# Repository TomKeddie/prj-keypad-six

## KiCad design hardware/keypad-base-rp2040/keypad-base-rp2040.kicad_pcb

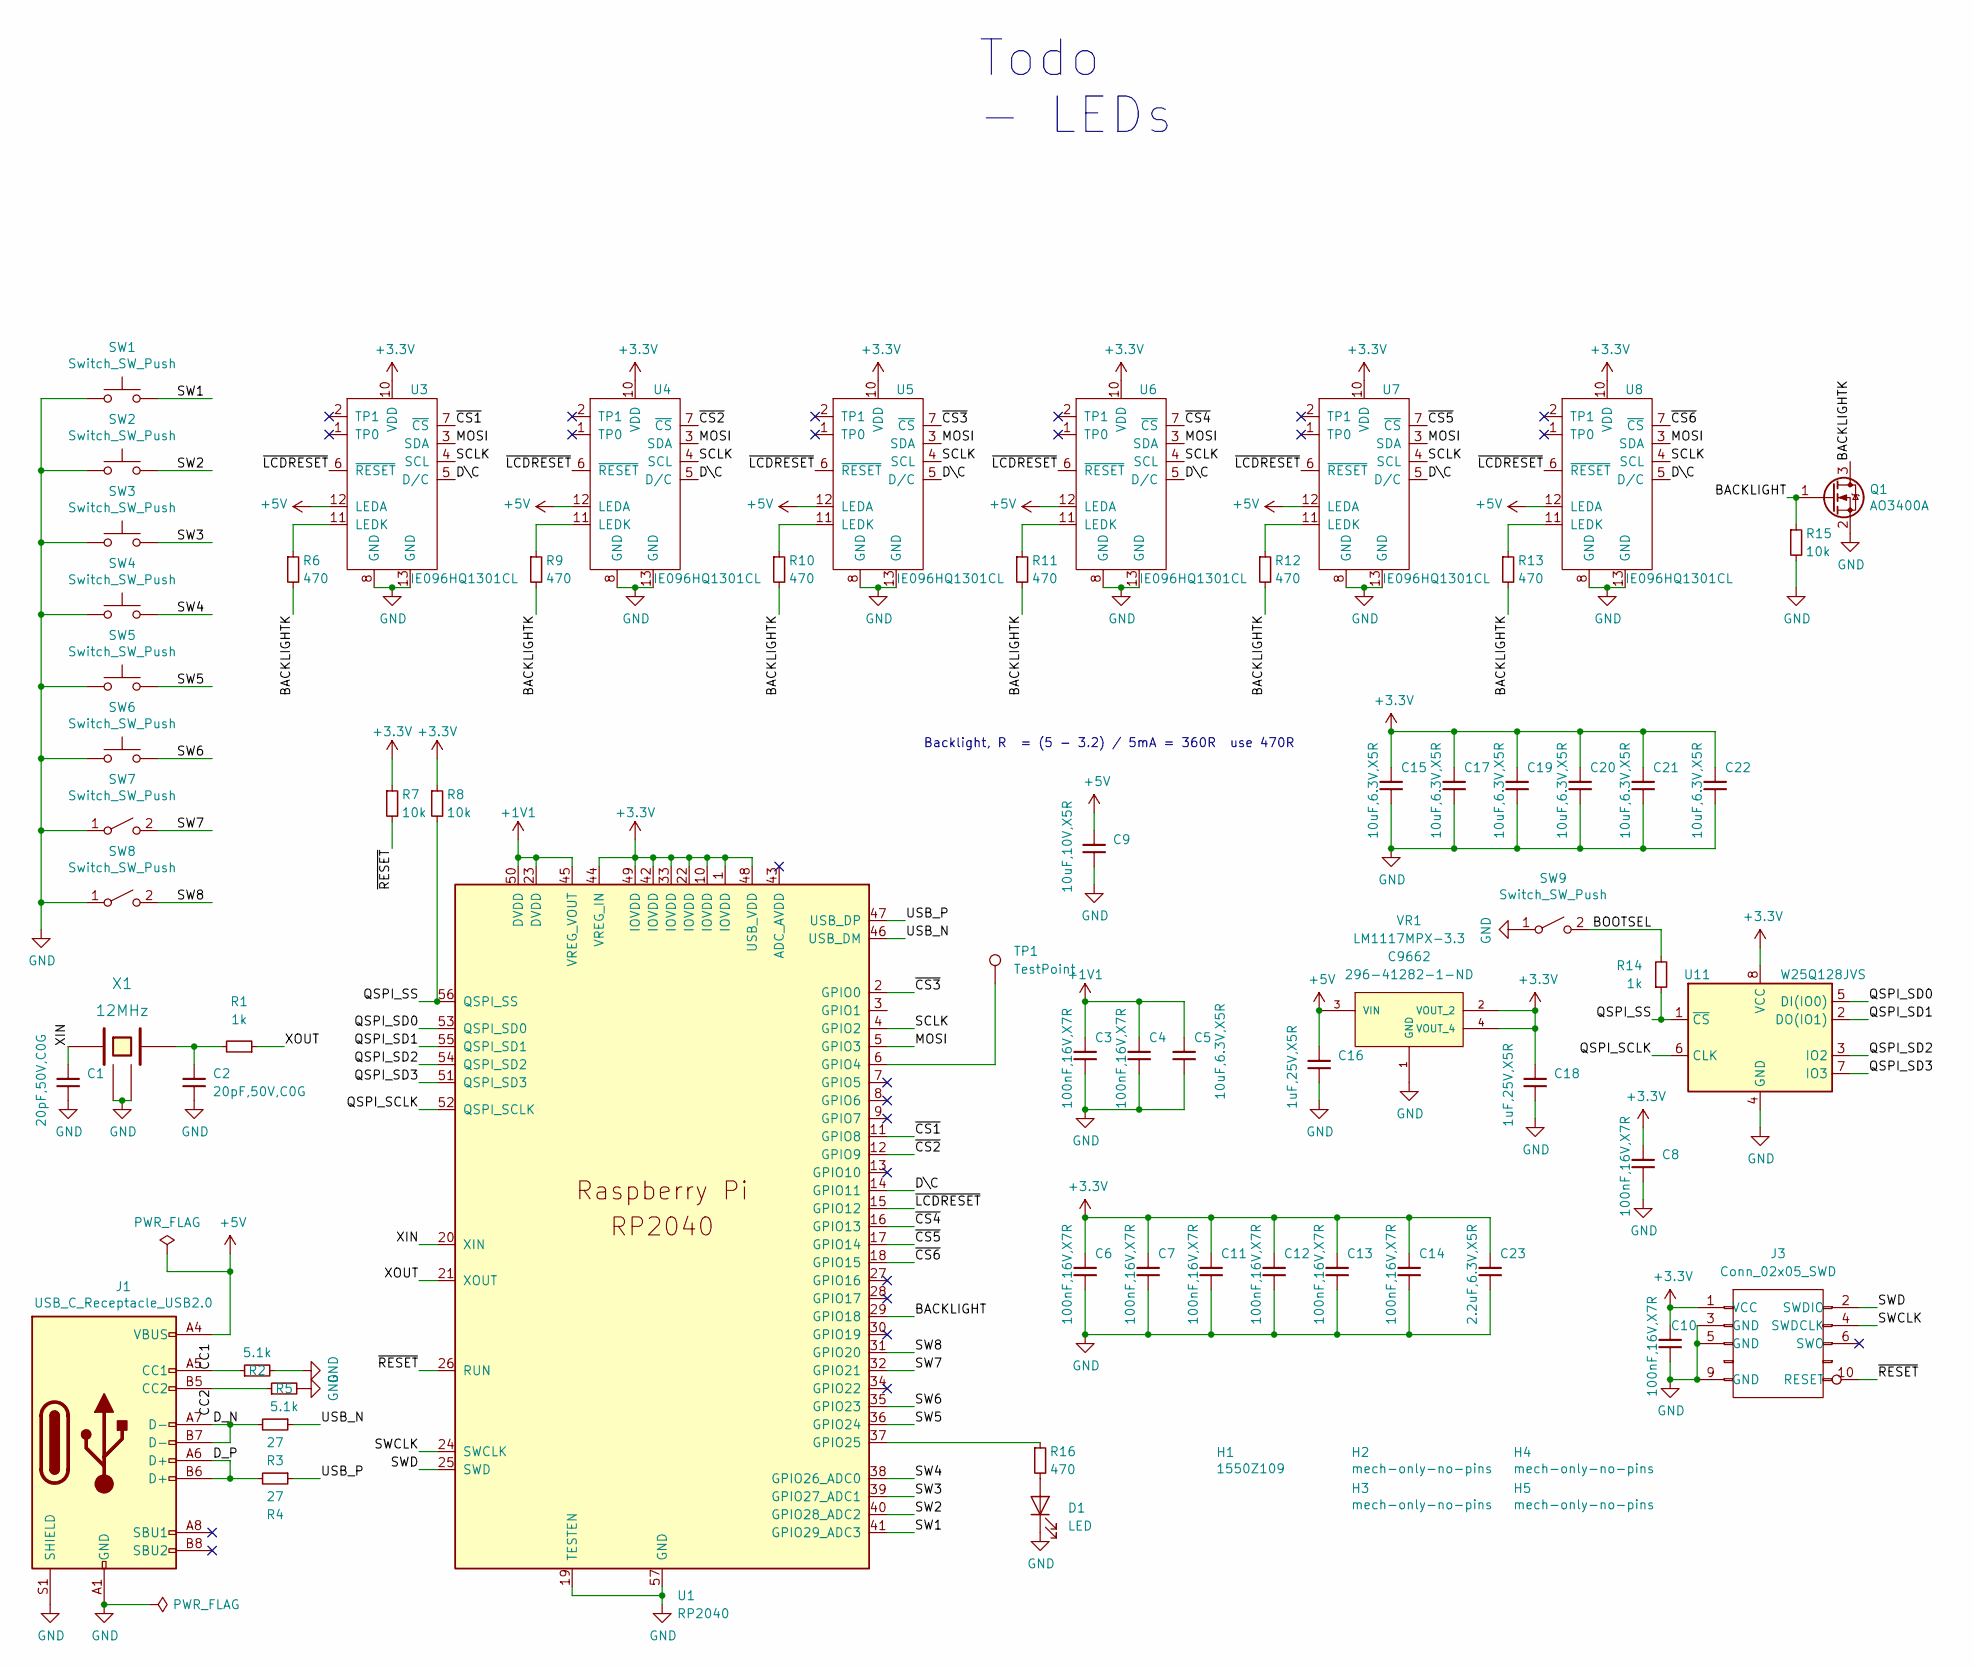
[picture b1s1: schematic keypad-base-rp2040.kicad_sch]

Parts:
C1, C2: 20pF,50V,C0G; C_0402_1005Metric; MFGPN 0402CG200J500NT; LCSC C1554
C3, C4, C6, C7, C8, C10, C11, C12, C13, C14: 100nF,16V,X7R; C_0402_1005Metric; MFGPN CL05B104KO5NNNC; LCSC C1525
C5, C15, C17, C19, C20, C21, C22: 10uF,6.3V,X5R; C_0402_1005Metric; MFGPN CL05A106MQ5NUNC; LCSC C15525
C9: 10uF,10V,X5R; C_0603_1608Metric; MFGPN CL10A106KP8NNNC; LCSC C19702
C16, C18: 1uF,25V,X5R; C_0402_1005Metric; MFGPN CL05A105KA5NQNC; LCSC C52923
C23: 2.2uF,6.3V,X5R; C_0402_1005Metric; MFGPN CL05A225MQ5NSNC; LCSC C12530
D1: LED; LED_0805_2012Metric; LCSC C2296
H1: 1550Z109
H2, H3, H4, H5: mech-only-no-pins; STUD_SOLDER_SMTSO_M3
J1: USB_C_Receptacle_USB2.0; USB_C_Receptacle_GT-USB-7010; LCSC C709357
J3: Conn_02x05_SWD; FTSH-105-01-F-DV-K
Q1: AO3400A; SOT-23; LCSC C20917
R1, R14: 1k; R_0402_1005Metric; MFGPN 0402WGF1001TCE; LCSC C11702
R2, R5: 5.1k; R_0402_1005Metric; MFGPN 0402WGF5101TCE; LCSC C25905
R3, R4: 27; R_0603_1608Metric; MFGPN 0603WAF270JT5E; LCSC C25190
R6, R9, R10, R11, R12, R13, R16: 470; R_0402_1005Metric; MFGPN 0402WGF4700TCE; LCSC C25117
R7, R8, R15: 10k; R_0402_1005Metric; MFGPN 0402WGF1002TCE; LCSC C25744
SW1, SW2, SW3, SW4, SW5, SW6: Switch_SW_Push; MX-KailhClip-1.00u-no-top-ring; LCSC C2803348
SW7, SW8, SW9: Switch_SW_Push; SW_SPST_SMD_SIDE_C319395; LCSC C319395
TP1: TestPoint; TestPoint_Pad_D1.0mm
U1: RP2040; RP2040-QFN-56; LCSC C2040
U3, U4, U5, U6, U7, U8: IE096HQ1301CL
U11: W25Q128JVS; SOIC-8_5.23x5.23mm_P1.27mm; LCSC C97521
VR1: LM1117MPX-3.3; VREG_LM1117MPX-3.3; PARTREV O; LCSC C9662
X1: 12MHz; Crystal_SMD_3225-4Pin_3.2x2.5mm; LCSC C9002

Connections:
+1V1: C3.1, C4.1, C5.1, U1.23 (DVDD), U1.45 (VREG_VOUT), U1.50 (DVDD)
+3.3V: C6.1, C7.1, C8.1, C10.1, C11.1, C12.1, C13.1, C14.1, C15.1, C17.1, C18.1, C19.1, C20.1, C21.1, C22.1, C23.1, J3.1 (VCC), R7.1, R8.1, U1.1 (IOVDD), U1.10 (IOVDD), U1.22 (IOVDD), U1.33 (IOVDD), U1.42 (IOVDD), U1.44 (VREG_IN), U1.48 (USB_VDD), U1.49 (IOVDD), U3.10 (VDD), U4.10 (VDD), U5.10 (VDD), U6.10 (VDD), U7.10 (VDD), U8.10 (VDD), U11.8 (VCC), VR1.2 (VOUT_2), VR1.4 (VOUT_4)
+5V: C9.1, C16.1, J1.A4 (VBUS), J1.A9 (VBUS), J1.B4 (VBUS), J1.B9 (VBUS), U3.12 (LEDA), U4.12 (LEDA), U5.12 (LEDA), U6.12 (LEDA), U7.12 (LEDA), U8.12 (LEDA), VR1.3 (VIN)
/BACKLIGHT: Q1.1 (G), R15.1, U1.29 (GPIO18)
/BACKLIGHTK: Q1.3 (D), R6.2, R9.2, R10.2, R11.2, R12.2, R13.2
/BOOTSEL: R14.2, SW9.2 (B)
/CC1: J1.A5 (CC1), R2.1
/CC2: J1.B5 (CC2), R5.1
/D\C: U1.14 (GPIO11), U3.5 (D/C), U4.5 (D/C), U5.5 (D/C), U6.5 (D/C), U7.5 (D/C), U8.5 (D/C)
/D_N: J1.A7 (D-), J1.B7 (D-), R3.2
/D_P: J1.A6 (D+), J1.B6 (D+), R4.2
/MOSI: U1.5 (GPIO3), U3.3 (SDA), U4.3 (SDA), U5.3 (SDA), U6.3 (SDA), U7.3 (SDA), U8.3 (SDA)
/QSPI_SCLK: U1.52 (QSPI_SCLK), U11.6 (CLK)
/QSPI_SD0: U1.53 (QSPI_SD0), U11.5 (DI(IO0))
/QSPI_SD1: U1.55 (QSPI_SD1), U11.2 (DO(IO1))
/QSPI_SD2: U1.54 (QSPI_SD2), U11.3 (IO2)
/QSPI_SD3: U1.51 (QSPI_SD3), U11.7 (IO3)
/QSPI_SS: R8.2, R14.1, U1.56 (QSPI_SS), U11.1 (~CS)
/SCLK: U1.4 (GPIO2), U3.4 (SCL), U4.4 (SCL), U5.4 (SCL), U6.4 (SCL), U7.4 (SCL), U8.4 (SCL)
/SW1: SW1.2, U1.41 (GPIO29_ADC3)
/SW2: SW2.2, U1.40 (GPIO28_ADC2)
/SW3: SW3.2, U1.39 (GPIO27_ADC1)
/SW4: SW4.2, U1.38 (GPIO26_ADC0)
/SW5: SW5.2, U1.36 (GPIO24)
/SW6: SW6.2, U1.35 (GPIO23)
/SW7: SW7.2 (B), U1.32 (GPIO21)
/SW8: SW8.2 (B), U1.31 (GPIO20)
/SWCLK: J3.4 (SWDCLK), U1.24 (SWCLK)
/SWD: J3.2 (SWDIO), U1.25 (SWD)
/USB_N: R3.1, U1.46 (USB_DM)
/USB_P: R4.1, U1.47 (USB_DP)
/XIN: C1.1, U1.20 (XIN), X1.1
/XOUT: R1.1, U1.21 (XOUT)
/~CS1: U1.11 (GPIO8), U3.7 (~CS)
/~CS2: U1.12 (GPIO9), U4.7 (~CS)
/~CS3: U1.2 (GPIO0), U5.7 (~CS)
/~CS4: U1.16 (GPIO13), U6.7 (~CS)
/~CS5: U1.17 (GPIO14), U7.7 (~CS)
/~CS6: U1.18 (GPIO15), U8.7 (~CS)
/~LCDRESET: U1.15 (GPIO12), U3.6 (~RESET), U4.6 (~RESET), U5.6 (~RESET), U6.6 (~RESET), U7.6 (~RESET), U8.6 (~RESET)
/~RESET: J3.10 (RESET), R7.2, U1.26 (RUN)
GND: C1.2, C2.2, C3.2, C4.2, C5.2, C6.2, C7.2, C8.2, C9.2, C10.2, C11.2, C12.2, C13.2, C14.2, C15.2, C16.2, C17.2, C18.2, C19.2, C20.2, C21.2, C22.2, C23.2, D1.1 (K), J1.A1 (GND), J1.A12 (GND), J1.B1 (GND), J1.B12 (GND), J1.S1 (SHIELD), J3.3 (GND), J3.5 (GND), J3.9 (GND), Q1.2 (S), R2.2, R5.2, R15.2, SW1.1, SW2.1, SW3.1, SW4.1, SW5.1, SW6.1, SW7.1 (A), SW8.1 (A), SW9.1 (A), U1.19 (TESTEN), U1.57 (GND), U3.8 (GND), U3.13 (GND), U4.8 (GND), U4.13 (GND), U5.8 (GND), U5.13 (GND), U6.8 (GND), U6.13 (GND), U7.8 (GND), U7.13 (GND), U8.8 (GND), U8.13 (GND), U11.4 (GND), VR1.1 (GND), X1.2 (GND), X1.4 (GND)
unnamed: C2.1, R1.2, X1.3
unnamed: D1.2 (A), R16.2
unnamed: R6.1, U3.11 (LEDK)
unnamed: R9.1, U4.11 (LEDK)
unnamed: R10.1, U5.11 (LEDK)
unnamed: R11.1, U6.11 (LEDK)
unnamed: R12.1, U7.11 (LEDK)
unnamed: R13.1, U8.11 (LEDK)
unnamed: R16.1, U1.37 (GPIO25)
unnamed: TP1.1, U1.6 (GPIO4)

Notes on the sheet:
Backlight, R = (5 - 3.2) / 5mA = 360R use 470R
Todo - LEDs

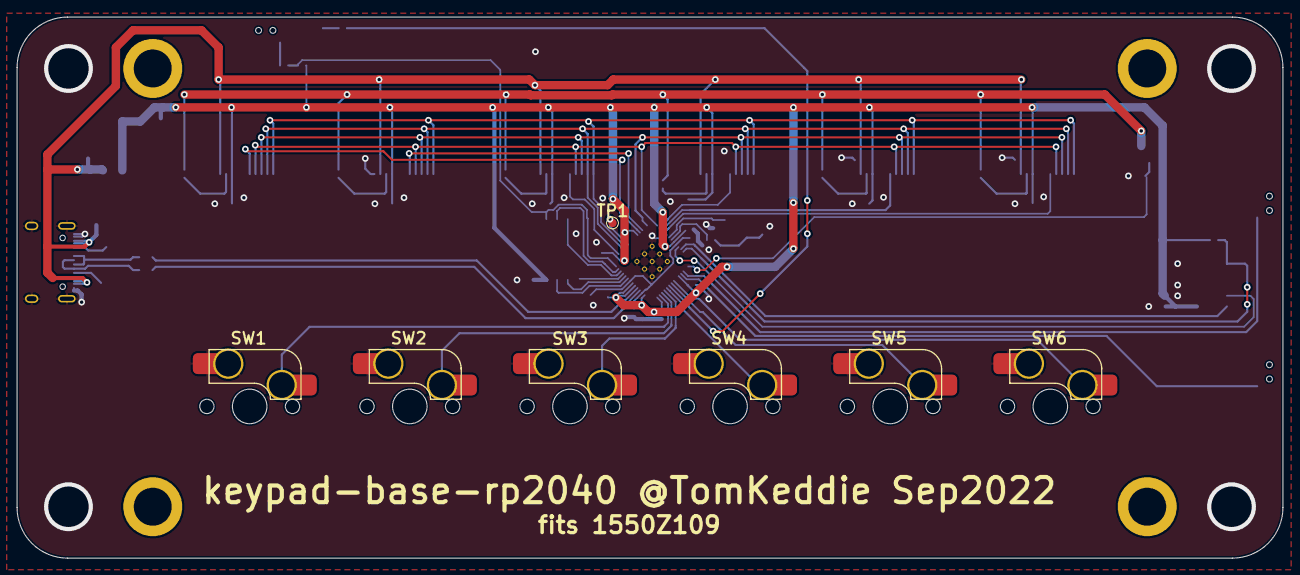
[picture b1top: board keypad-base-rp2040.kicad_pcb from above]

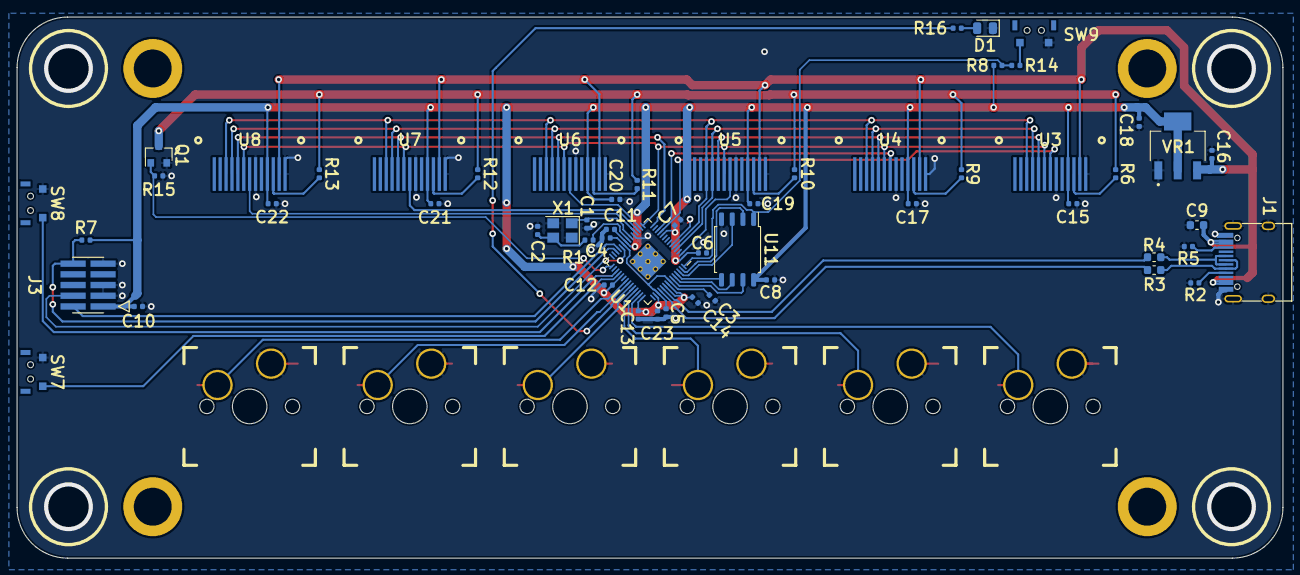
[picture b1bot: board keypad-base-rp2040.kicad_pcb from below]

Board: 2 copper layers, 150.2 x 64.2 mm, 68 parts (60 on the bottom side), 52 nets.

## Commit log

2021-04-25 keypad-base: new design
2021-04-25 keypad-base: reduced to 6 keys, add mode change side buttons
2021-04-25 keypad-base: Apr2021 release
2021-04-25 keypad-frame: Apr2021 release of keypad frame
2021-04-25 keypad-base: fix silk, add missing edge cuts layer
2021-04-26 keypad-base/keypad-frame: change to M2 standoffs, Apr2021a release
2021-05-30 keypad-frame: May2021 release, change to m3 holes, shrink keyswitch cutouts
2021-06-06 keypad-base: Jun2021 - change standoff type
2022-01-17 Fix submodules & restructure dirs
2022-01-18 keypad-six-test: 2 buttons working, 6 keys working, spi test
2022-01-19 hardware: directory restructure
2022-01-19 software: add test for spi flash
2022-01-19 software/keypad-six-test: backlight control working (active high)
2022-01-22 software/keypad-six-test: add lcd driver with test image
2022-01-22 software/keypad-six-test: add remaining display chip selects
2022-08-25 hardware: add missing keypad-base files
2022-08-25 hardware: move keyboard io footprints to parent dir
2022-08-25 hardware: keypad-base-rp2040 from keypad-base
2022-08-25 hardware/keypad-base-rp2040: update to latest kicad file format
2022-08-28 hardware/keypad0base-rp2040: first pass at rp2040 based design
2022-09-03 hardware/keypad-base-rp2040: progress commit
2022-09-04 hardware/keypad-base-rp2040: placed, routed, ERC & DRC clean
2022-09-04 hardware/keypad-frame: Sep2022a version
    Reduced keyswitch opening by 0.2mm
2022-09-04 hardare/keypad-base-rp2040: Sep2022 as submitted

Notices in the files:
parts and their libraries:
Copyright 2016 Accelerated Designs. All rights reserved.
